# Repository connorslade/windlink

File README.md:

# windlink

System to show wind data on a Garmin watch for sailing.
Work in progress.

## References

- [The CANBoat project PGN documentation](https://canboat.github.io/canboat/canboat.html)

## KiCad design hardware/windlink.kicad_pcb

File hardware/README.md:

# hardware

[View PCB / Schematic with KiCanvas](https://kicanvas.org/?repo=https%3A%2F%2Fgithub.com%2Fconnorslade%2Fwindlink%2Ftree%2Fmain%2Fhardware)

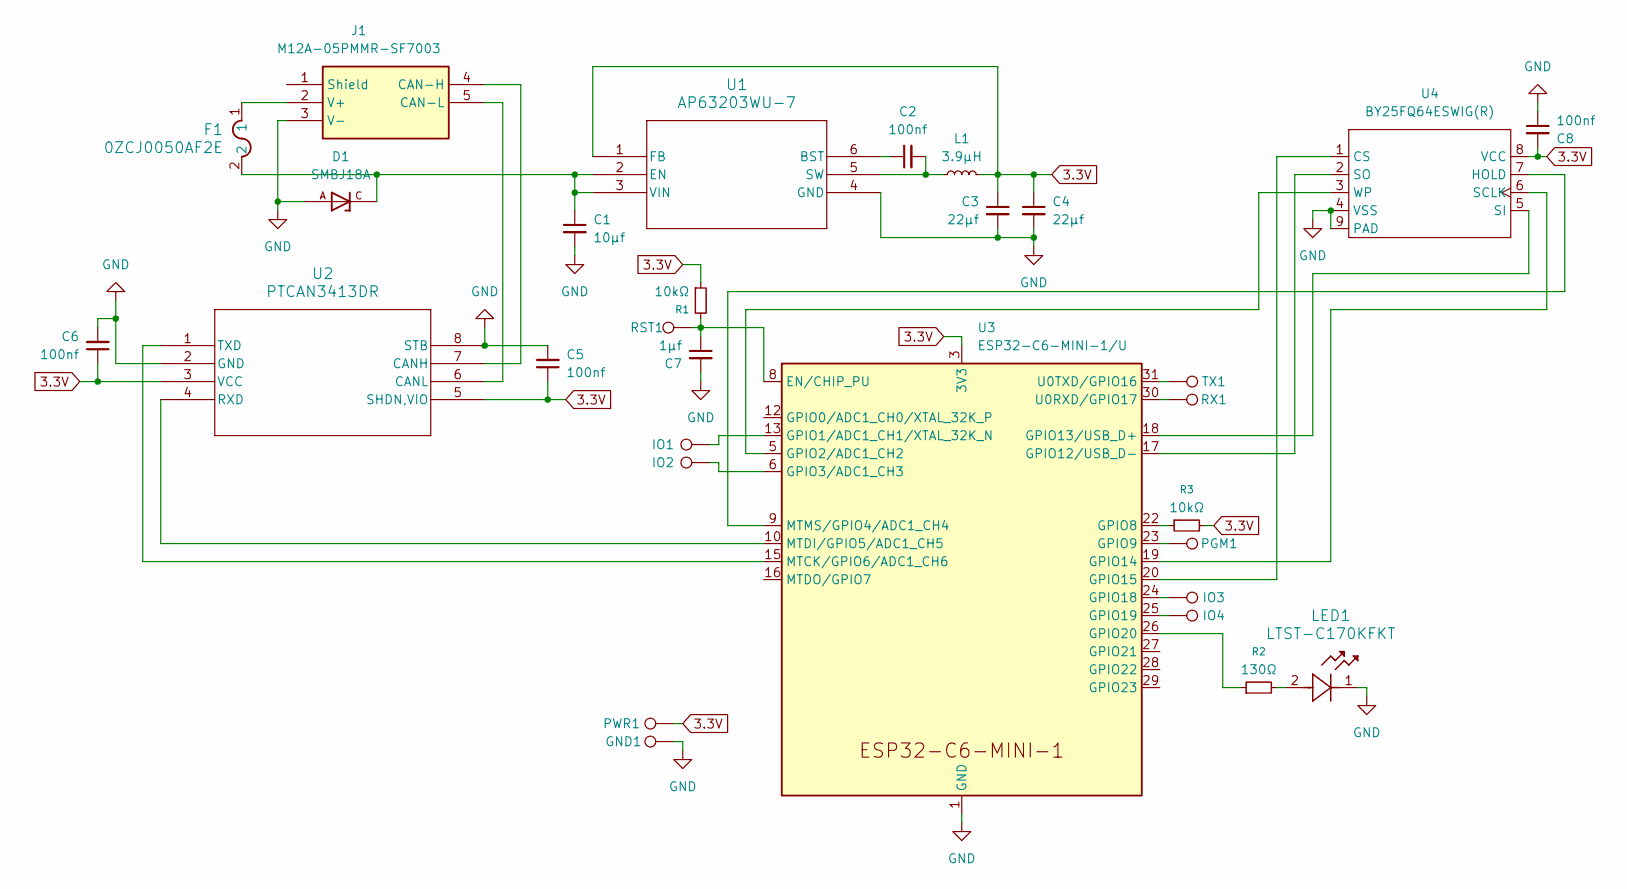
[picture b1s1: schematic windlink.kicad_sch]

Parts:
C1: 10μf; C_0805_2012Metric_Pad1.18x1.45mm_HandSolder
C2, C5, C6, C8: 100nf; C_0805_2012Metric_Pad1.18x1.45mm_HandSolder
C3, C4: 22μf; C_0805_2012Metric_Pad1.18x1.45mm_HandSolder
C7: 1μf; C_0805_2012Metric_Pad1.18x1.45mm_HandSolder
D1: SMBJ18A; DIOM4336X265N; PARTREV F2102
F1: 0ZCJ0050AF2E; 0ZCJ_BEL
GND1: TestPoint; TestPoint_Pad_D2.0mm
IO1, IO2, IO3, IO4: TestPoint; TestPoint_Pad_D2.0mm
J1: M12A-05PMMR-SF7003; M12A05PMMRSF7003; Manufacturer_Part_Number M12A-05PMMR-SF7003
L1: 3.9μH; IND_TAIYO_LBM2016_TAY
LED1: LTST-C170KFKT; LED_LTST-C170KFKT_LTO
PGM1: TestPoint; TestPoint_Pad_D2.0mm
PWR1: TestPoint; TestPoint_Pad_D2.0mm
R1, R3: 10kΩ; R_0805_2012Metric_Pad1.20x1.40mm_HandSolder
R2: 130Ω; R_0805_2012Metric_Pad1.20x1.40mm_HandSolder
RST1: TestPoint; TestPoint_Pad_D2.0mm
RX1: TestPoint; TestPoint_Pad_D2.0mm
TX1: TestPoint; TestPoint_Pad_D2.0mm
U1: AP63203WU-7; AP63203WU-7_DIO
U2: PTCAN3413DR; SOIC8_D_TEX
U3: ESP32-C6-MINI-1/U; ESP32-C6-MINI-1
U4: BY25FQ64ESWIG(R)

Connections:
3.3V: C3.1, C4.1, C5.1, C6.1, C8.2, L1.2, PWR1.1, R1.1, R3.2, U1.1 (FB), U2.3 (VCC), U2.5 (SHDN,VIO), U3.3 (3V3), U4.8 (VCC)
GND: C1.2, C3.2, C4.2, C5.2, C6.2, C7.2, C8.1, D1.A, GND1.1, J1.3 (V-), LED1.1, U1.4 (GND), U2.2 (GND), U2.8 (STB), U3.1 (GND), U3.2 (GND), U3.11 (GND), U3.14 (GND), U3.36 (GND), U3.37 (GND), U3.38 (GND), U3.39 (GND), U3.40 (GND), U3.41 (GND), U3.42 (GND), U3.43 (GND), U3.44 (GND), U3.45 (GND), U3.46 (GND), U3.47 (GND), U3.48 (GND), U3.49 (GND), U3.50 (GND), U3.51 (GND), U3.52 (GND), U3.53 (GND), U4.4 (VSS), U4.9 (PAD)
unnamed: F1.1, J1.2 (V+)
unnamed: LED1.2, R2.2
unnamed: C2.1, U1.6 (BST)
unnamed: C1.1, D1.C, F1.2, U1.2 (EN), U1.3 (VIN)
unnamed: C2.2, L1.1, U1.5 (SW)
unnamed: J1.4 (CAN-H), U2.7 (CANH)
unnamed: J1.5 (CAN-L), U2.6 (CANL)
unnamed: U2.4 (RXD), U3.10 (MTDI/GPIO5/ADC1_CH5)
unnamed: U2.1 (TXD), U3.15 (MTCK/GPIO6/ADC1_CH6)
unnamed: C7.1, R1.2, RST1.1, U3.8 (EN/CHIP_PU)
unnamed: IO1.1, U3.13 (GPIO1/ADC1_CH1/XTAL_32K_N)
unnamed: U3.5 (GPIO2/ADC1_CH2), U4.3 (WP)
unnamed: IO2.1, U3.6 (GPIO3/ADC1_CH3)
unnamed: R3.1, U3.22 (GPIO8)
unnamed: PGM1.1, U3.23 (GPIO9)
unnamed: U3.17 (GPIO12/USB_D-), U4.2 (SO)
unnamed: U3.18 (GPIO13/USB_D+), U4.5 (SI)
unnamed: U3.19 (GPIO14), U4.6 (SCLK)
unnamed: U3.20 (GPIO15), U4.1 (CS)
unnamed: IO3.1, U3.24 (GPIO18)
unnamed: IO4.1, U3.25 (GPIO19)
unnamed: R2.1, U3.26 (GPIO20)
unnamed: U3.9 (MTMS/GPIO4/ADC1_CH4), U4.7 (HOLD)
unnamed: RX1.1, U3.30 (U0RXD/GPIO17)
unnamed: TX1.1, U3.31 (U0TXD/GPIO16)

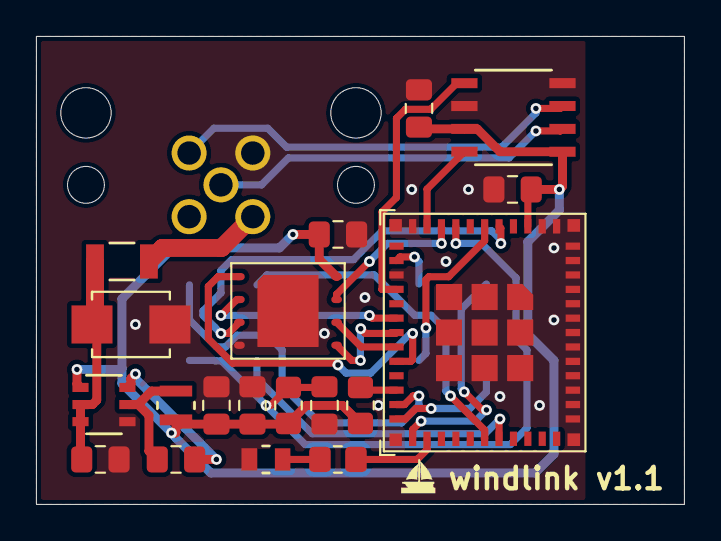
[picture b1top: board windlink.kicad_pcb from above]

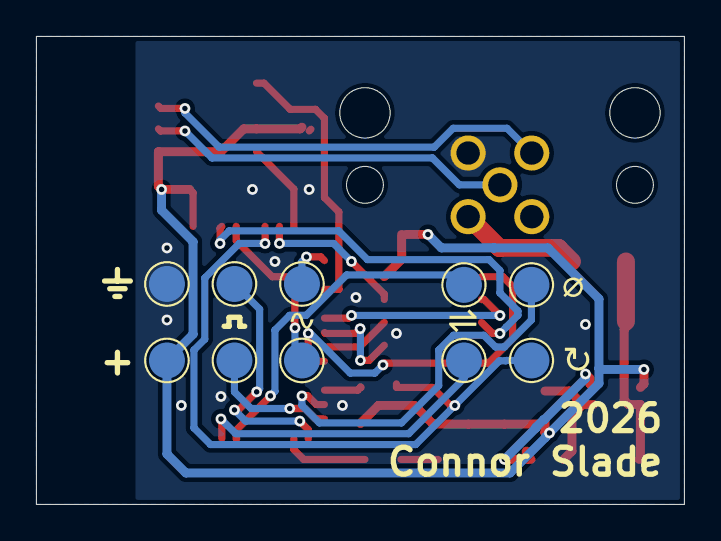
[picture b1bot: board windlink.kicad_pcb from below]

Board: 2 copper layers, 36.0 x 26.0 mm, 30 parts (10 on the bottom side), 27 nets.

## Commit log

2026-04-20 Working connection from watch
2026-04-20 Split packets by screen
2026-04-21 Fast packets
2026-04-21 Correctly response to requests for address claims
2026-04-21 New nmea2000 code on embeded
2026-04-25 Add hardware files (PCB / Case)
2026-04-25 Status LED
2026-04-25 Watch UI Progress
2026-04-26 Redesign case
2026-04-28 Indicator system
2026-04-29 Rework case design
2026-04-30 WiFi interface
2026-04-30 WiFi OTA Updates
2026-04-30 Fix typo
2026-04-30 Draft TCP CAN interface
2026-04-30 Move embedded modules into folder
2026-05-01 Wireless can interface
2026-05-03 Add frame destination
2026-05-09 Simrad autopilot control progress
2026-05-11 PCB: Add extra flash and antenna cutout
2026-05-16 PCB: Finilize v1.1
2026-05-16 PCB: Breakout jig
